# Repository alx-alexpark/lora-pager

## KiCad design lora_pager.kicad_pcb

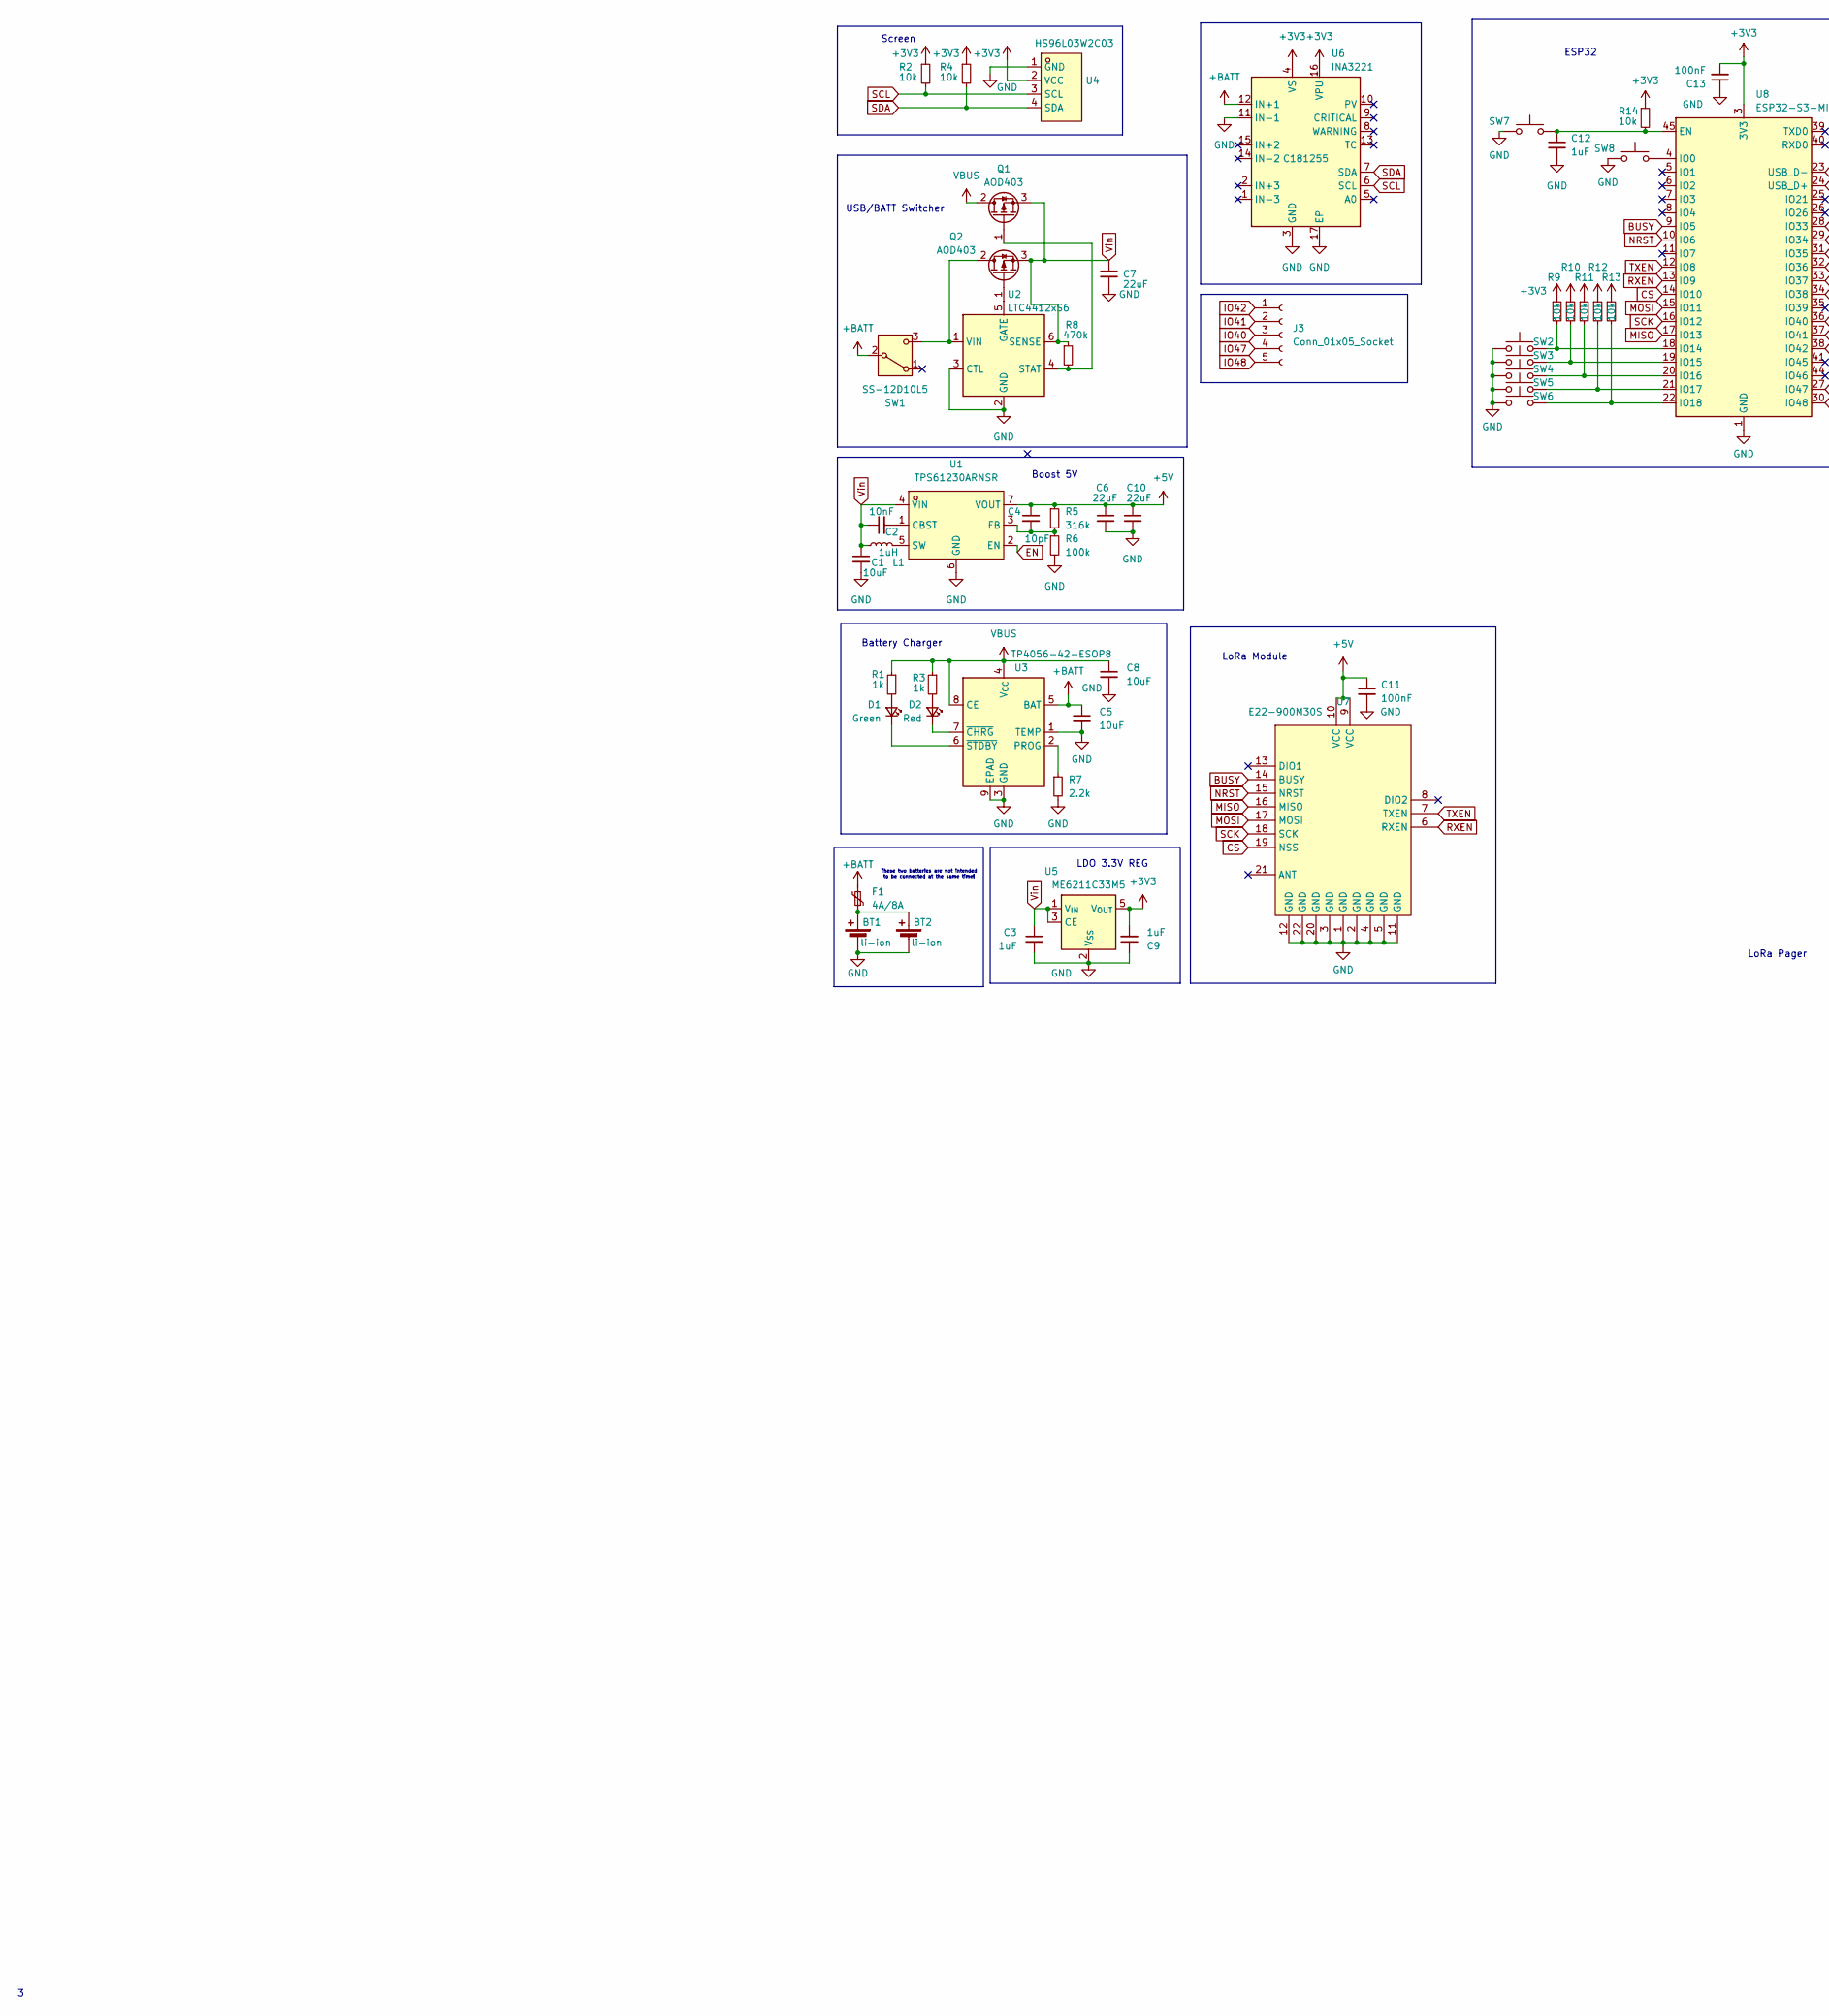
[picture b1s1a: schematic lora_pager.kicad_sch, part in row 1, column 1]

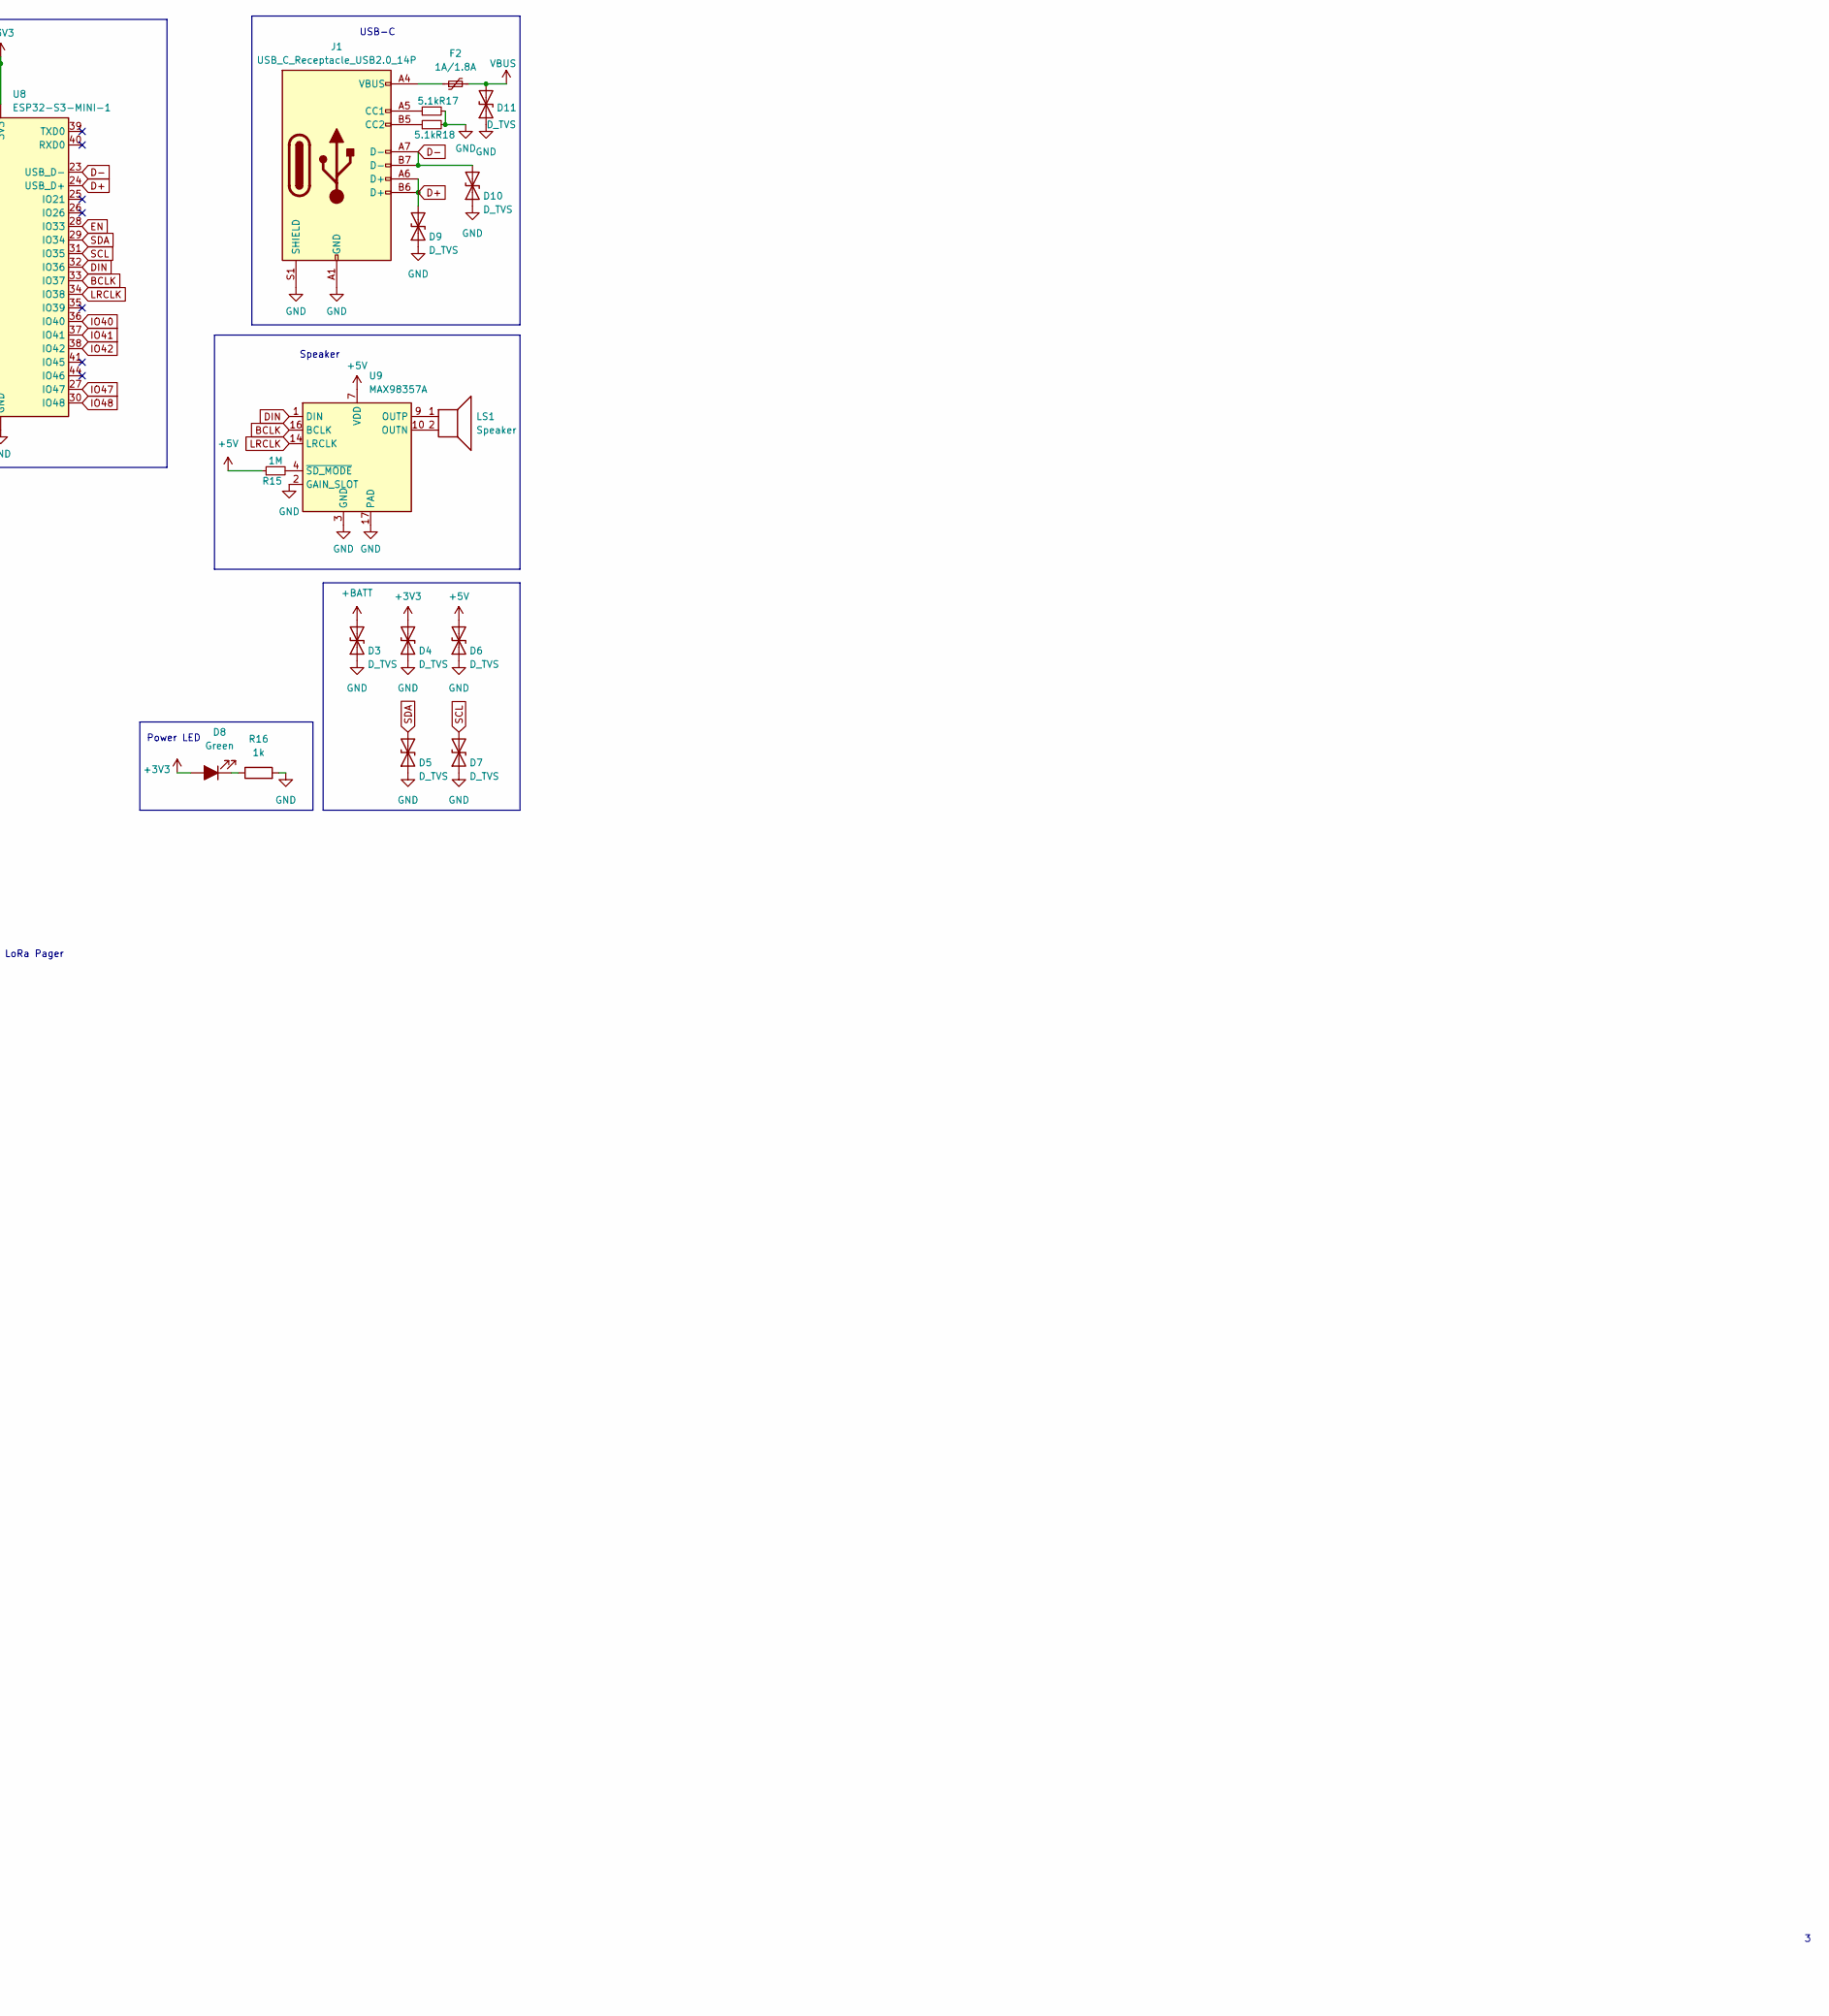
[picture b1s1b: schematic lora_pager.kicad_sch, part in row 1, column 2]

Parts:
BT1: li-ion; JST_PH_B2B-PH-K_1x02_P2.00mm_Vertical; LCSC Part C131337
BT2: li-ion; BATTERY-SMD_18650-1S-L77.1-W20.7-1; LCSC Part C2988620
C1, C5, C8: 10uF; C_0805_2012Metric_Pad1.18x1.45mm_HandSolder; LCSC Part C15850
C2: 10nF; C_0402_1005Metric_Pad0.74x0.62mm_HandSolder; LCSC Part C60133
C3, C9, C12: 1uF; C_0402_1005Metric_Pad0.74x0.62mm_HandSolder; LCSC Part C14445
C4: 10pF; C_0402_1005Metric_Pad0.74x0.62mm_HandSolder; LCSC Part C106199
C6, C7, C10: 22uF; C_0805_2012Metric_Pad1.18x1.45mm_HandSolder; LCSC Part C5674
C11, C13: 100nF; C_0402_1005Metric_Pad0.74x0.62mm_HandSolder; LCSC Part C1525
D1: Green; LED_0805_2012Metric_Pad1.15x1.40mm_HandSolder; LCSC Part C2297
D2: Red; LED_0805_2012Metric_Pad1.15x1.40mm_HandSolder; LCSC Part C84256
D3, D4, D5, D6, D7, D9, D10, D11: D_TVS; D_SOD-923; LCSC Part C96512
D8: Green; LED_0603_1608Metric; LCSC Part C2286
F1: 4A/8A; Fuse_1812_4532Metric_Pad1.30x3.40mm_HandSolder; LCSC Part C22374900
F2: 1A/1.8A; Fuse_1206_3216Metric_Pad1.42x1.75mm_HandSolder; LCSC Part C70082
J1: USB_C_Receptacle_USB2.0_14P; USB_C_Receptacle_G-Switch_GT-USB-7010ASV; LCSC Part C2988369
J3: Conn_01x05_Socket; PinHeader_1x05_P2.54mm_Vertical
L1: 1uH; WE-MAPI_4020; Digikey 732-8228-2-ND
LS1: Speaker; BUZ-SMD_4P-L13.0-W13.0-P11.4-BL; LCSC Part C18186315
Q1, Q2: AOD403; TO-252-2; LCSC Part C5224305
R1, R3, R16: 1k; R_0402_1005Metric_Pad0.72x0.64mm_HandSolder; LCSC Part C11702
R2, R4, R9, R10, R11, R12, R13, R14: 10k; R_0402_1005Metric_Pad0.72x0.64mm_HandSolder; LCSC Part C60490
R5: 316k; R_0402_1005Metric_Pad0.72x0.64mm_HandSolder; LCSC Part C2998151
R6: 100k; R_0603_1608Metric_Pad0.98x0.95mm_HandSolder; LCSC Part C14675
R7: 2.2k; R_0603_1608Metric_Pad0.98x0.95mm_HandSolder; LCSC Part C114662
R8: 470k; R_0603_1608Metric_Pad0.98x0.95mm_HandSolder; LCSC Part C114622
R15: 1M; R_0402_1005Metric_Pad0.72x0.64mm_HandSolder; LCSC Part C138033
R17, R18: 5.1k; R_0603_1608Metric_Pad0.98x0.95mm_HandSolder; LCSC Part C23186
SW1: SS-12D10L5; SW-TH_SS-12D10L5; LCSC Part C319012
SW2, SW3, SW4, SW5, SW6, SW7, SW8: TS-1089S-02526; SW-SMD_4P-L4.2-W3.3-P2.15-LS5.1; LCSC Part C455282
U1: TPS61230ARNSR; VQFN-7_L2.1-W2.1-P0.50-BL; LCSC Part C376005
U2: LTC4412xS6; TSOT-23-6; LCSC Part C521306
U3: TP4056-42-ESOP8; SOIC-8-1EP_3.9x4.9mm_P1.27mm_EP2.41x3.3mm_ThermalVias; LCSC Part C16581
U4: HS96L03W2C03; OLED-TH_L27.8-W27.2-P2.54_C9900033791; LCSC Part C5248080
U5: ME6211C33M5; SOT-23-5; LCSC Part C82942
U6: INA3221; Texas_RGV0016A_VQFN-16-1EP_4x4mm_P0.65mm_EP2.1x2.1mm; LCSC Part C181255
U7: E22-900M30S; WIRELM-SMD_E22-900M30S; LCSC Part C411294
U8: ESP32-S3-MINI-1; ESP32-S2-MINI-1; LCSC Part C2913206
U9: MAX98357A; TQFN-16-1EP_3x3mm_P0.5mm_EP1.23x1.23mm; LCSC Part C910544

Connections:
+3V3: C9.2, C13.2, D4.2 (A2), D8.2 (A), R2.1, R4.1, R9.1, R10.1, R11.1, R12.1, R13.1, R14.1, U4.2 (VCC), U5.5 (V_{OUT}), U6.4 (VS), U6.16 (VPU), U8.3 (3V3)
+5V: C4.1, C6.1, C10.1, C11.1, D6.2 (A2), R5.1, R15.1, U1.7 (VOUT), U7.9 (VCC), U7.10 (VCC), U9.7 (VDD), U9.8 (VDD)
+BATT: C5.1, D3.2 (A2), F1.2, SW1.2 (B), U3.5 (BAT), U6.12 (IN+1)
BCLK: U8.33 (IO37), U9.16 (BCLK)
BUSY: U7.14 (BUSY), U8.9 (IO5)
CS: U7.19 (NSS), U8.14 (IO10)
D+: D9.2 (A2), J1.A6 (D+), J1.B6 (D+), U8.24 (USB_D+)
D-: D10.2 (A2), J1.A7 (D-), J1.B7 (D-), U8.23 (USB_D-)
DIN: U8.32 (IO36), U9.1 (DIN)
EN: U1.2 (EN), U8.28 (IO33)
GND: BT1.2 (-), BT2.2 (-), C1.2, C3.2, C5.2, C6.2, C7.2, C8.2, C9.1, C10.2, C11.2, C12.2, C13.1, D3.1 (A1), D4.1 (A1), D5.1 (A1), D6.1 (A1), D7.1 (A1), D9.1 (A1), D10.1 (A1), D11.1 (A1), J1.A1 (GND), J1.A12 (GND), J1.B1 (GND), J1.B12 (GND), J1.S1 (SHIELD), R6.2, R7.2, R16.2, R17.2, R18.2, SW2.1, SW3.1, SW4.1, SW5.1, SW6.1, SW7.1, SW8.1, U1.6 (GND), U2.2 (GND), U2.3 (CTL), U3.1 (TEMP), U3.3 (GND), U3.9 (EPAD), U4.1 (GND), U5.2 (V_{SS}), U6.3 (GND), U6.11 (IN-1), U6.17 (EP), U7.1 (GND), U7.2 (GND), U7.3 (GND), U7.4 (GND), U7.5 (GND), U7.11 (GND), U7.12 (GND), U7.20 (GND), U7.22 (GND), U8.1 (GND), U8.2 (GND), U8.42 (GND), U8.43 (GND), U8.46 (GND), U8.47 (GND), U8.48 (GND), U8.49 (GND), U8.50 (GND), U8.51 (GND), U8.52 (GND), U8.53 (GND), U8.54 (GND), U8.55 (GND), U8.56 (GND), U8.57 (GND), U8.58 (GND), U8.59 (GND), U8.60 (GND), U8.61 (GND), U8.62 (GND), U8.63 (GND), U8.64 (GND), U8.65 (GND), U9.2 (GAIN_SLOT), U9.3 (GND), U9.11 (GND), U9.15 (GND), U9.17 (PAD)
IO40: J3.3, U8.36 (IO40)
IO41: J3.2, U8.37 (IO41)
IO42: J3.1, U8.38 (IO42)
IO47: J3.4, U8.27 (IO47)
IO48: J3.5, U8.30 (IO48)
LRCLK: U8.34 (IO38), U9.14 (LRCLK)
MISO: U7.16 (MISO), U8.17 (IO13)
MOSI: U7.17 (MOSI), U8.15 (IO11)
NRST: U7.15 (NRST), U8.10 (IO6)
unnamed: BT1.1 (+), BT2.1 (+), F1.1
unnamed: D1.2 (A), R1.2
unnamed: D1.1 (K), U3.6 (~STDBY)
unnamed: D2.2 (A), R3.2
unnamed: D2.1 (K), U3.7 (~CHRG)
unnamed: D8.1 (K), R16.1
unnamed: F2.1, J1.A4 (VBUS), J1.A9 (VBUS), J1.B4 (VBUS), J1.B9 (VBUS)
unnamed: J1.A5 (CC1), R17.1
unnamed: J1.B5 (CC2), R18.1
unnamed: Q1.1 (G), R8.2, U2.4 (STAT)
unnamed: Q2.2 (D), SW1.3 (C), U2.1 (VIN)
unnamed: Q2.1 (G), U2.5 (GATE)
unnamed: C2.2, U1.1 (CBST)
unnamed: C4.2, R5.2, R6.1, U1.3 (FB)
unnamed: L1.2, U1.5 (SW)
unnamed: R7.1, U3.2 (PROG)
unnamed: C12.1, R14.2, SW7.2, U8.45 (EN)
unnamed: SW8.2, U8.4 (IO0)
unnamed: R9.2, SW2.2, U8.18 (IO14)
unnamed: R10.2, SW3.2, U8.19 (IO15)
unnamed: R11.2, SW4.2, U8.20 (IO16)
unnamed: R12.2, SW5.2, U8.21 (IO17)
unnamed: R13.2, SW6.2, U8.22 (IO18)
unnamed: LS1.2, U9.10 (OUTN)
unnamed: LS1.1, U9.9 (OUTP)
unnamed: R15.2, U9.4 (~SD_MODE)
RXEN: U7.6 (RXEN), U8.13 (IO9)
SCK: U7.18 (SCK), U8.16 (IO12)
SCL: D7.2 (A2), R2.2, U4.3 (SCL), U6.6 (SCL), U8.31 (IO35)
SDA: D5.2 (A2), R4.2, U4.4 (SDA), U6.7 (SDA), U8.29 (IO34)
TXEN: U7.7 (TXEN), U8.12 (IO8)
VBUS: C8.1, D11.2 (A2), F2.2, Q1.2 (D), R1.1, R3.1, U3.4 (V_{CC}), U3.8 (CE)
Vin: C1.1, C2.1, C3.1, C7.1, L1.1, Q1.3 (S), Q2.3 (S), R8.1, U1.4 (VIN), U2.6 (SENSE), U5.1 (V_{IN}), U5.3 (CE)

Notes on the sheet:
LDO 3.3V REG
Screen
Power LED
Battery Charger
LoRa Module
USB-C
LoRa Pager
ESP32
Speaker
Boost 5V
These two batteries are not intended to be connected at the same time!
USB/BATT Switcher

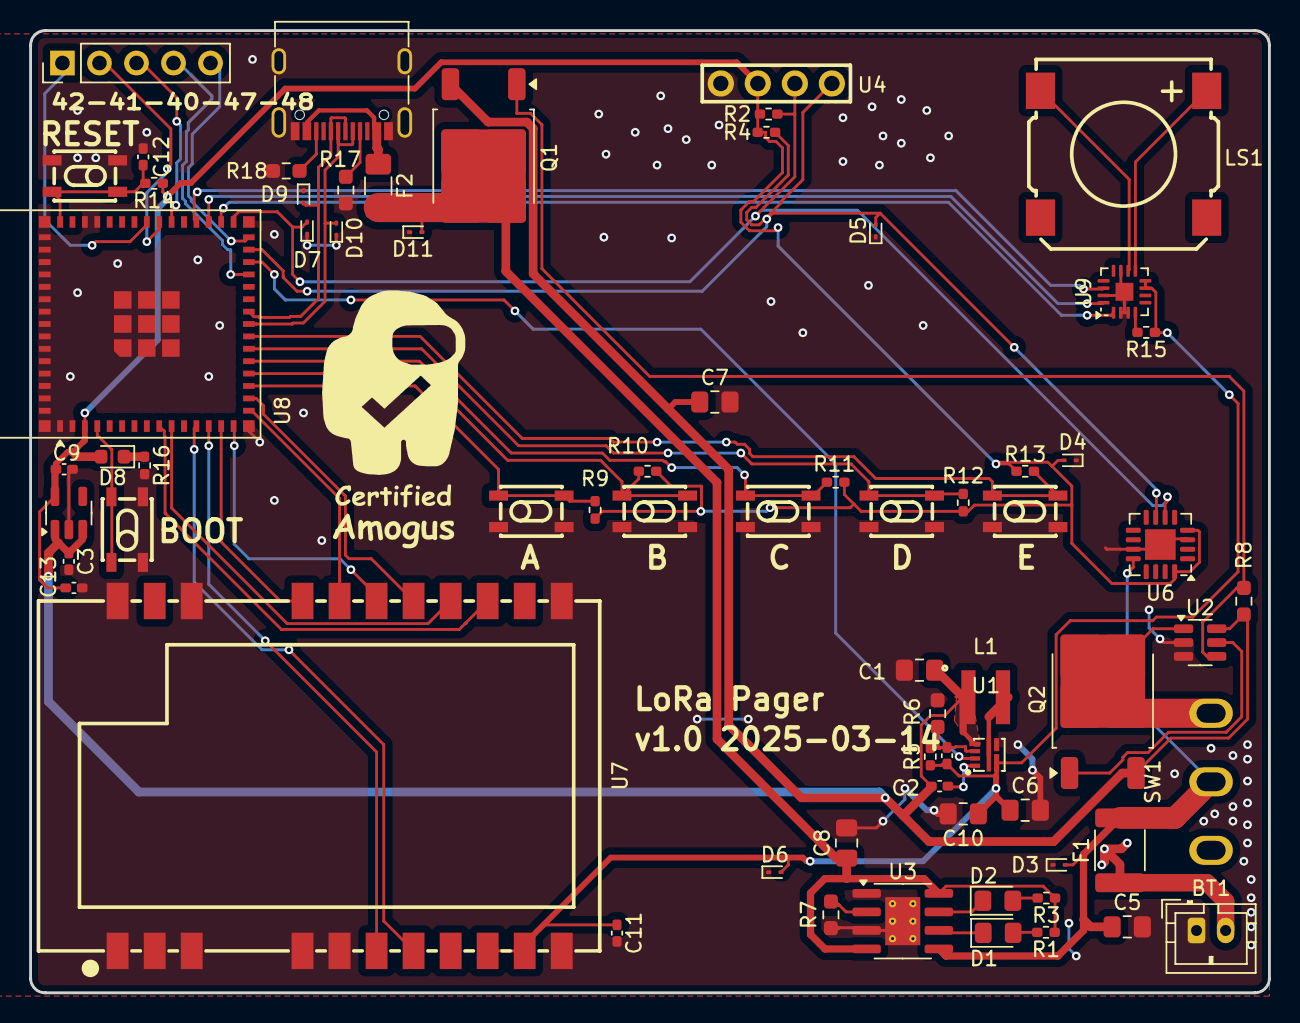
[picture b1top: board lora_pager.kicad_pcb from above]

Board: 2 copper layers, 85.0 x 66.0 mm, 69 parts (1 on the bottom side), 53 nets.

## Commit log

2025-03-11 sus commit
2025-03-12 Finished first rough draft
2025-03-13 almost done :siren-thumbsup:
2025-03-15 Final product: version 1 has been ordered
